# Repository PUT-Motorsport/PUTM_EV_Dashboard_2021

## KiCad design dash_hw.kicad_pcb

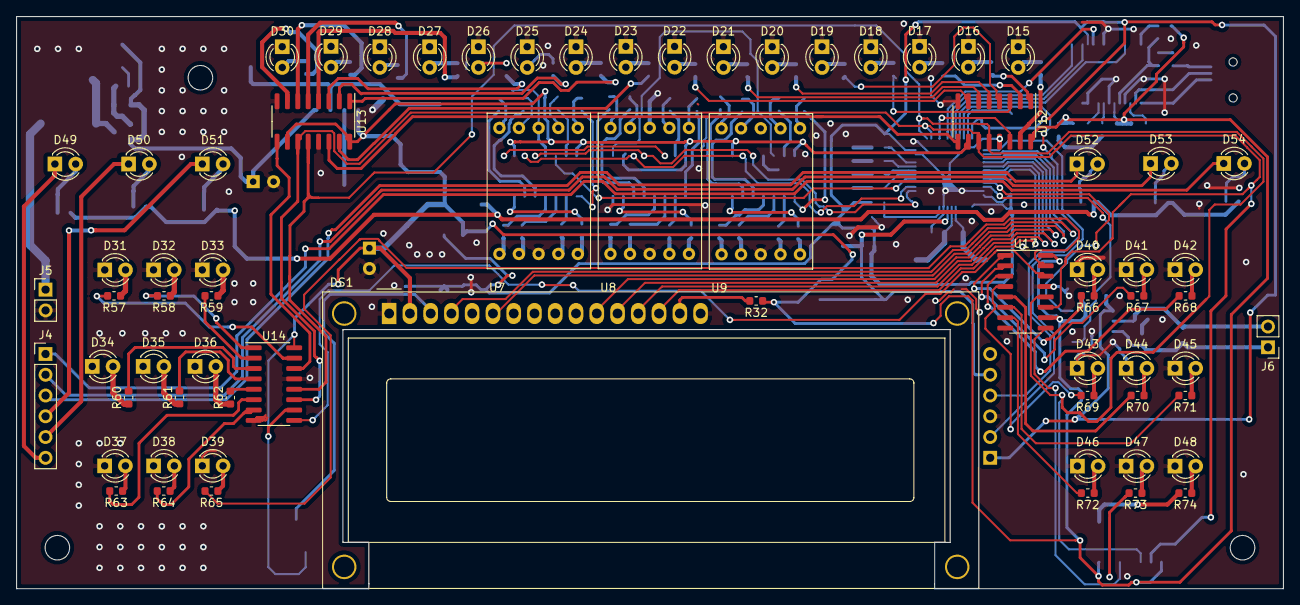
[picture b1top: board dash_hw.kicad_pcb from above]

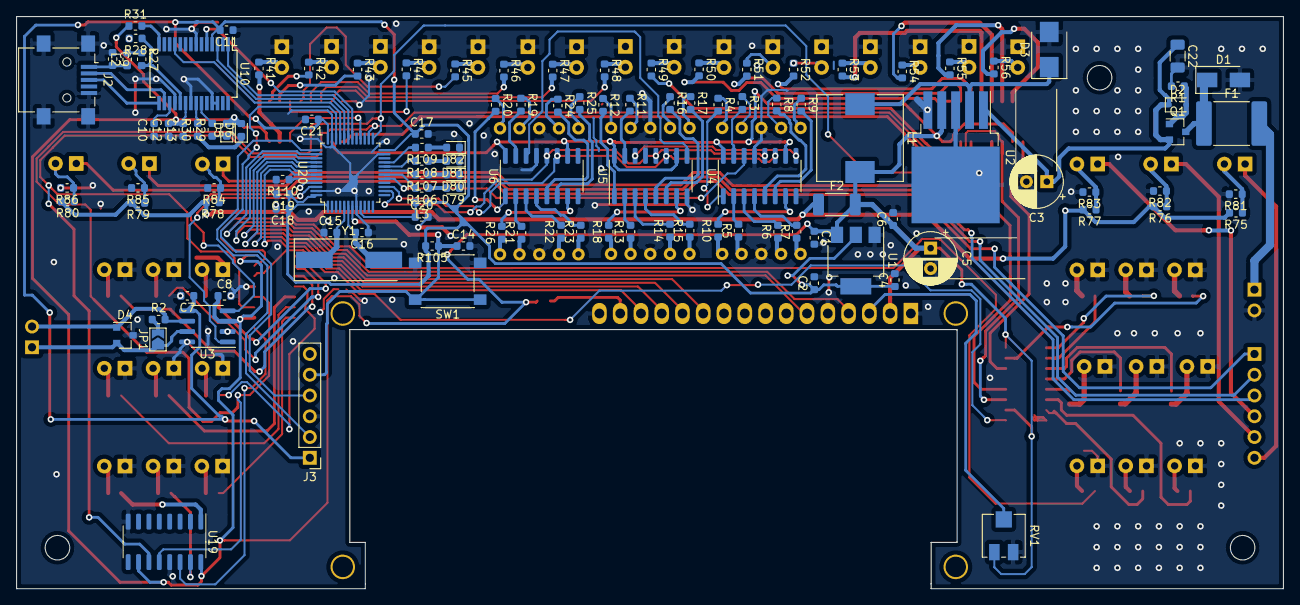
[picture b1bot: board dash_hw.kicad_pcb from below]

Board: 2 copper layers, 155.0 x 70.0 mm, 188 parts (118 on the bottom side), 192 nets.

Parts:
C1, C2, C7, C10, C11, C13, C14, C17, C18, C19, C20: 100nF; C_0603_1608Metric
C3: 100uF; CP_Radial_D6.3mm_P2.50mm
C4, C6, C8: 1uF; C_0603_1608Metric
C5: 220uF; CP_Radial_D6.3mm_P2.50mm
C9: 10nF; C_0603_1608Metric
C12, C21: 4.7uF; C_0603_1608Metric
C15, C16: 22pF; C_0603_1608Metric
C22: 470nF; C_1206_3216Metric
D1: SMAJ24CA; D_SMA
D2: MM3Z12VST1G; D_SOD-323
D3: D_Schottky; D_SMB
D4: PESD2CAN.215; SOT-23
D5: TXLED; LED_0603_1608Metric
D6: RXLED; LED_0603_1608Metric
D15, D16, D17, D18, D19, D20, D21, D22, D23, D24, D25, D26, D27, D28, D29, D30, D31, D32, D33, D34, D35, D36, D37, D38, D39, D40, D41, D42, D43, D44, D45, D46, D47, D48: LED; LED_D3.0mm_Clear
D49, D50, D51, D52, D53, D54: LED_Small; LED_D3.0mm_Clear
D79, D80, D81, D82: LED; LED_0603_1608Metric
DS1: WC1602A
F1: SL150-33 1.5A; Fuse_2920_7451Metric
F2: Polyfuse; Fuse_2010_5025Metric
J2: USB_B_Mini; USB_Mini-B_Lumberg_2486_01_Horizontal
J3: Conn_01x06_Male; PinHeader_1x06_P2.54mm_Vertical
J4: Conn_01x06_Female; PinHeader_1x06_P2.54mm_Vertical
J5, J6: Conn_01x02; PinHeader_1x02_P2.54mm_Vertical
JP1: a; SolderJumper-2_P1.3mm_Open_TrianglePad1.0x1.5mm
L1: 68uH; L_10.4x10.4_H4.8
L2: KoralikFerrytowy; L_0603_1608Metric
L3: 10uH; L_0603_1608Metric
Q1: DMP3056L-7; SOT-23
R1, R28, R31, R105, R110: 10k; R_0603_1608Metric
R2: 120R; R_0603_1608Metric
R3, R4, R5, R6, R7, R8, R9, R10, R11, R12, R13, R14, R15, R16, R17, R18, R19, R20, R21, R22, R23, R24, R25, R26: 330; R_0603_1608Metric
R27: 4k7; R_0603_1608Metric
R29, R30: 560R; R_0603_1608Metric
R32: 0R; R_0603_1608Metric
R41, R42, R43, R44, R45, R46, R47, R48, R49, R50, R51, R52, R53, R54, R55, R56, R57, R58, R59, R60, R61, R62, R63, R64, R65, R66, R67, R68, R69, R70, R71, R72, R73, R74: 200; R_0603_1608Metric
R75, R76, R77, R78, R79, R80: 200R; C_0603_1608Metric
R81, R82, R83, R84, R85, R86: R_Small; C_0603_1608Metric
R106, R107, R108, R109: 620; R_0603_1608Metric
RV1: 10k; Potentiometer_Vishay_TS53YJ_Vertical
SW1: SW_Push; SW_Push_1P1T_NO_6x6mm_H9.5mm
U1: LM1117-3.3; SOT-223-3_TabPin2
U2: LM2596S-5; TO-263-5_TabPin3
U3: MCP2562-H-SN; SOIC-8_3.9x4.9mm_P1.27mm
U4, U5, U6, U12, U13, U14, U17, U19: 74HC595; SOIC-16_3.9x9.9mm_P1.27mm
U7, U8, U9: OPS-S5621; 0.56” Case Mold Type LED Display
U10: FT232RL; SSOP-28_5.3x10.2mm_P0.65mm
U20: STM32F103C8Tx; LQFP-48_7x7mm_P0.5mm
Y1: Crystal; Crystal_SMD_HC49-SD

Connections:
5Vfused: F2.1, R75.2, R76.2, R77.2, R78.2, R79.2, R80.2
+3V3: C2.1, C4.1, C7.1, C11.2, C17.1, C18.1, C19.1, C21.1, J3.1, L3.1, R105.2, U1.2, U3.5, U10.4, U20.1, U20.24, U20.36, U20.48
+5V: C1.1, C5.1, C6.1, C8.1, C12.2, C13.2, D5.2, D6.2, DS1.2, F2.2, L1.2, R31.1, R32.1, RV1.3, U1.3, U2.4, U3.3, U4.10, U4.16, U5.10, U5.16, U6.10, U6.16, U10.20, U12.10, U12.16, U13.10, U13.16, U14.10, U14.16, U17.10, U17.16, U19.10, U19.16
/CANH: D4.2, J6.1, JP1.1, U3.7
/CANL: D4.1, J6.2, R2.2, U3.6
/CAN_RX: U3.4, U20.45
/CAN_TX: U3.1, U20.46
/GLV+: F1.2, J5.1
/SPI_1_CLK: U4.11, U5.11, U6.11, U20.15
/SPI_1_CS: U4.12, U5.12, U6.12, U20.14
/SPI_1_MOSI: U4.14, U20.17
/SPI_2_CLK: U12.11, U13.11, U14.11, U17.11, U19.11, U20.26
/SPI_2_CS: U12.12, U13.12, U14.12, U17.12, U19.12, U20.25
/SPI_2_MOSI: U12.14, U20.28
/UART_CTS: U10.3, U20.32
/UART_RTS: U10.11, U20.33
/UART_RX: U10.1, U20.31
/UART_TX: U10.5, U20.30
/charge_level/QH': U13.9, U14.14
/display_16x2/D4: DS1.11, U20.40
/display_16x2/D5: DS1.12, U20.41
/display_16x2/D6: DS1.13, U20.42
/display_16x2/D7: DS1.14, U20.43
/display_16x2/E: DS1.6, U20.39
/mcu/LCD_RS: DS1.4, U20.38
/mcu/SW_CLK: J3.2, U20.37
/mcu/SW_DIO: J3.4, U20.34
/mcu/SW_NRST: C14.1, J3.5, R105.1, SW1.1, U20.7
FAULT1: D54.1, J4.1
FAULT2: D53.1, J4.2
FAULT3: D52.1, J4.3
FAULT4: D51.1, J4.4
FAULT5: D50.1, J4.5
FAULT6: D49.1, J4.6
GND: C1.2, C2.2, C3.2, C4.2, C5.2, C6.2, C7.2, C8.2, C9.1, C10.1, C11.1, C12.1, C13.1, C14.2, C15.1, C16.1, C17.2, C18.2, C19.2, C20.2, C21.2, C22.2, D1.2, D3.2, D4.3, D15.1, D16.1, D17.1, D18.1, D19.1, D20.1, D21.1, D22.1, D23.1, D24.1, D25.1, D26.1, D27.1, D28.1, D29.1, D30.1, D31.1, D32.1, D33.1, D34.1, D35.1, D36.1, D37.1, D38.1, D39.1, D40.1, D41.1, D42.1, D43.1, D44.1, D45.1, D46.1, D47.1, D48.1, D79.1, D80.1, D81.1, D82.1, DS1.1, DS1.5, DS1.16, J2.5, J2.6, J3.3, J5.2, R1.2, R28.2, R81.2, R82.2, R83.2, R84.2, R85.2, R86.2, R110.2, RV1.1, SW1.2, U1.1, U2.3, U2.5, U3.2, U3.8, U4.8, U4.13, U5.8, U5.13, U6.8, U6.13, U7.3, U7.8, U8.3, U8.8, U9.3, U9.8, U10.7, U10.18, U10.21, U10.25, U10.26, U12.8, U12.13, U13.8, U13.13, U14.8, U14.13, U17.8, U17.13, U19.8, U19.13, U20.8, U20.23, U20.35, U20.47
unnamed: C9.2, J2.1, L2.1
unnamed: C10.2, U10.17
unnamed: C15.2, U20.5, Y1.1
unnamed: C16.2, U20.6, Y1.2
unnamed: C20.1, L3.2, U20.9
unnamed: C3.1, C22.1, D2.1, Q1.2, U2.1
unnamed: D1.1, F1.1, Q1.3
unnamed: D2.2, Q1.1, R1.1
unnamed: D3.1, L1.1, U2.2
unnamed: D5.1, R29.1
unnamed: D6.1, R30.1
unnamed: D15.2, R41.1
unnamed: D16.2, R42.1
unnamed: D17.2, R43.1
unnamed: D18.2, R44.1
unnamed: D19.2, R45.1
unnamed: D20.2, R46.1
unnamed: D21.2, R47.1
unnamed: D22.2, R48.1
unnamed: D23.2, R49.1
unnamed: D24.2, R50.1
unnamed: D25.2, R51.1
unnamed: D26.2, R52.1
unnamed: D27.2, R53.1
unnamed: D28.2, R54.1
unnamed: D29.2, R55.1
unnamed: D30.2, R56.1
unnamed: D31.2, R57.1
unnamed: D32.2, R58.1
unnamed: D33.2, R59.1
unnamed: D34.2, R60.1
unnamed: D35.2, R61.1
unnamed: D36.2, R62.1
unnamed: D37.2, R63.1
unnamed: D38.2, R64.1
unnamed: D39.2, R65.1
unnamed: D40.2, R66.1
unnamed: D41.2, R67.1
unnamed: D42.2, R68.1
unnamed: D43.2, R69.1
unnamed: D44.2, R70.1
unnamed: D45.2, R71.1
unnamed: D46.2, R72.1
unnamed: D47.2, R73.1
unnamed: D48.2, R74.1
unnamed: D49.2, R75.1, R81.1
unnamed: D50.2, R76.1, R82.1
unnamed: D51.2, R77.1, R83.1
unnamed: D52.2, R78.1, R84.1
unnamed: D53.2, R79.1, R85.1
unnamed: D54.2, R80.1, R86.1
unnamed: D79.2, R106.1
unnamed: D80.2, R107.1
unnamed: D81.2, R108.1
unnamed: D82.2, R109.1
unnamed: DS1.3, RV1.2
unnamed: DS1.15, R32.2
unnamed: J2.2, U10.16
unnamed: J2.3, U10.15
unnamed: JP1.2, R2.1
unnamed: L2.2, R27.1
unnamed: R3.1, U7.7
unnamed: R3.2, U4.15
unnamed: R4.1, U7.6
unnamed: R4.2, U4.1
unnamed: R5.1, U7.4
unnamed: R5.2, U4.2
unnamed: R6.1, U7.2
unnamed: R6.2, U4.3
unnamed: R7.1, U7.1
unnamed: R7.2, U4.4
unnamed: R8.1, U7.9
unnamed: R8.2, U4.5
unnamed: R9.1, U7.10
unnamed: R9.2, U4.6
unnamed: R10.1, U7.5
unnamed: R10.2, U4.7
unnamed: R11.1, U8.7
unnamed: R11.2, U5.15
unnamed: R12.1, U8.6
unnamed: R12.2, U5.1
unnamed: R13.1, U8.4
unnamed: R13.2, U5.2
unnamed: R14.1, U8.2
unnamed: R14.2, U5.3
unnamed: R15.1, U8.1
unnamed: R15.2, U5.4
unnamed: R16.1, U8.9
unnamed: R16.2, U5.5
unnamed: R17.1, U8.10
unnamed: R17.2, U5.6
unnamed: R18.1, U8.5
unnamed: R18.2, U5.7
unnamed: R19.1, U9.7
unnamed: R19.2, U6.15
unnamed: R20.1, U9.6
unnamed: R20.2, U6.1
unnamed: R21.1, U9.4
unnamed: R21.2, U6.2
unnamed: R22.1, U9.2
unnamed: R22.2, U6.3
unnamed: R23.1, U9.1
unnamed: R23.2, U6.4
unnamed: R24.1, U9.9
unnamed: R24.2, U6.5
unnamed: R25.1, U9.10
unnamed: R25.2, U6.6
unnamed: R26.1, U9.5
unnamed: R26.2, U6.7
unnamed: R27.2, R28.1, U10.19
unnamed: R29.2, U10.23
unnamed: R30.2, U10.22
unnamed: R31.2, U10.14
unnamed: R41.2, U12.15
unnamed: R42.2, U12.1
unnamed: R43.2, U12.2
unnamed: R44.2, U12.3
unnamed: R45.2, U12.4
unnamed: R46.2, U12.5
unnamed: R47.2, U12.6
unnamed: R48.2, U12.7
unnamed: R49.2, U13.15
unnamed: R50.2, U13.1
unnamed: R51.2, U13.2
unnamed: R52.2, U13.3
unnamed: R53.2, U13.4
unnamed: R54.2, U13.5
unnamed: R55.2, U13.6
unnamed: R56.2, U13.7
unnamed: R57.2, U14.15
unnamed: R58.2, U14.1
unnamed: R59.2, U14.2
unnamed: R60.2, U14.3
unnamed: R61.2, U14.4
unnamed: R62.2, U14.5
unnamed: R63.2, U14.6
unnamed: R64.2, U14.7
unnamed: R65.2, U17.15
unnamed: R66.2, U17.1
unnamed: R67.2, U17.2
unnamed: R68.2, U17.3
unnamed: R69.2, U17.4
unnamed: R70.2, U17.5
unnamed: R71.2, U17.6
unnamed: R72.2, U17.7
unnamed: R73.2, U19.15
unnamed: R74.2, U19.1
unnamed: R106.2, U20.18
unnamed: R107.2, U20.19
unnamed: R108.2, U20.20
unnamed: R109.2, U20.21
unnamed: R110.1, U20.44
unnamed: U4.9, U5.14
unnamed: U5.9, U6.14
unnamed: U12.9, U13.14
unnamed: U14.9, U17.14
unnamed: U17.9, U19.14

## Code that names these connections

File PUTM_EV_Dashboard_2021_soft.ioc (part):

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Mcu.Name=STM32F103C(8-B)Tx
Mcu.Package=LQFP48
Mcu.UserName=STM32F103C8Tx
PA0-WKUP.Signal=ADCx_IN0
PA10.Mode=Asynchronous
PA10.Signal=USART1_RX
PA11.Mode=CTS_RTS
PA11.Signal=USART1_CTS
PA12.Mode=CTS_RTS
PA12.Signal=USART1_RTS
PA13.Mode=Serial_Wire
PA13.Signal=SYS_JTMS-SWDIO
PA14.Mode=Serial_Wire
PA14.Signal=SYS_JTCK-SWCLK
PA15.GPIOParameters=GPIO_Label
PA15.GPIO_Label=LCD_RS
PA15.Signal=GPIO_Output
PA4.GPIOParameters=GPIO_Label
PA4.GPIO_Label=SPI1_NSS
PA4.Signal=GPIO_Output
PA5.Mode=Full_Duplex_Master
PA5.Signal=SPI1_SCK
PA6.Mode=Full_Duplex_Master
PA6.Signal=SPI1_MISO
PA7.Mode=Full_Duplex_Master
PA7.Signal=SPI1_MOSI
PA9.Mode=Asynchronous
PA9.Signal=USART1_TX
PB12.GPIOParameters=GPIO_Label
PB12.GPIO_Label=SPI2_NSS
PB12.Signal=GPIO_Output
PB13.Mode=Full_Duplex_Master
PB13.Signal=SPI2_SCK
PB14.Mode=Full_Duplex_Master
PB14.Signal=SPI2_MISO
PB15.Mode=Full_Duplex_Master
PB15.Signal=SPI2_MOSI
PB3.GPIOParameters=GPIO_Label
PB3.GPIO_Label=LCD_E
PB3.Signal=GPIO_Output
PB4.GPIOParameters=GPIO_Label
PB4.GPIO_Label=LCD_D4
PB4.Signal=GPIO_Output
PB5.GPIOParameters=GPIO_Label
PB5.GPIO_Label=LCD_D5
PB5.Signal=GPIO_Output
PB6.GPIOParameters=GPIO_Label
PB6.GPIO_Label=LCD_D6
PB6.Signal=GPIO_Output
PB7.GPIOParameters=GPIO_Label
PB7.GPIO_Label=LCD_D7
PB7.Signal=GPIO_Output
PB8.Mode=CAN_Activate
PB8.Signal=CAN_RX
PB9.Mode=CAN_Activate
PB9.Signal=CAN_TX
RCC.SYSCLKFreq_VALUE=32000000
RCC.SYSCLKSource=RCC_SYSCLKSOURCE_PLLCLK
board=custom

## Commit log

2020-11-28 init commit
2020-11-28 kicad dash project
2020-11-28 added lib files
2020-12-07 reorganized schematic; added reverse polarity protection; start adding footprints
2020-12-19 footprints; library for 7seg; start pcb layout
2021-01-10 remove double elements in 3state leds
2021-01-10 one more input capacitor
2021-01-23 some new
2021-03-31 Added some headers and data preparation
2021-04-06 added preparing data
2021-04-21 Added LCD support Need testing and update (timer)
2021-04-21 Hardware update Approved
2021-04-25 Added digits to 7seg
2021-05-03 Updated hardware
2021-05-03 SMD elements labels layeout updated
2021-05-11 Added test template
2021-05-24 LCD Disp driver
2021-05-25 test function
2021-05-26 added drivers and linker file
2021-05-30 Button handling
2021-06-15 added sendAlfaNum
2021-06-20 wrong formating
2021-06-22 refactor, HV send as percentages
2021-06-22 Added displaying HV percentages
2021-06-22 cleanup
2021-06-25 disp update, hot fixes, offets, hv/speed
2021-06-28 7seg OK, LED are working
2021-06-28 changes from master
2021-06-28 HV big LED works
2021-06-28 fixed offets, LED works
2021-07-08 slower alfanum disp update
2021-07-22 Added some frames
2021-07-22 added TS State LEC
2021-09-25 added gitignore
2021-09-25 added all files
